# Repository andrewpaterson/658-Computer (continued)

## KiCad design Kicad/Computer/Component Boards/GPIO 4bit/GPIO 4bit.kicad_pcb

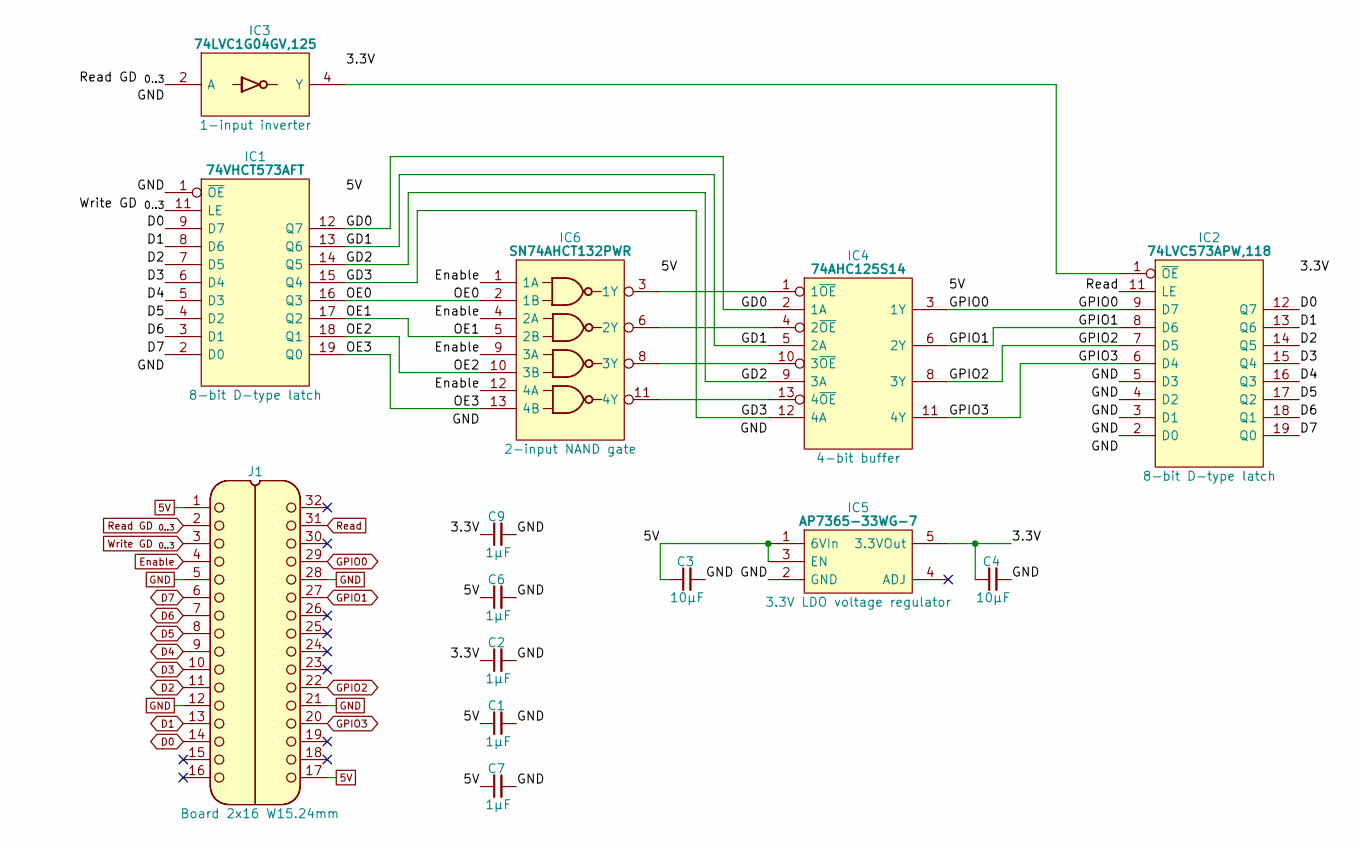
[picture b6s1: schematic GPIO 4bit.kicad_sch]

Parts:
C1, C2, C6, C7, C9: 1μF; C_0805
C3, C4: 10µF; C_0805
IC1: 74VHCT573AFT; SOP65P640X120-20N; Manufacturer_Part_Number 74VHCT573AFT; Mouser Part Number N/A
IC2: 74LVC573APW,118; SOP65P640X110-20N; Mouser Part Number 771-74LVC573APW-T
IC3: 74LVC1G04GV,125; SOT95P275X110-5N; Manufacturer_Part_Number 74LVC1G04GV,125; Mouser Part Number 771-74LVC1G04GV
IC4: 74AHC125S14; SOIC127P600X173-14N; Manufacturer_Part_Number 74AHC125S14-13; Mouser Part Number 621-74AHC125S14-13
IC5: AP7365-33WG-7; SOT95P285X130-5N; Manufacturer_Part_Number AP7365-33WG-7; Mouser Part Number 621-AP7365-33WG-7
IC6: SN74AHCT132PWR; SOP65P640X120-14N; Manufacturer_Part_Number SN74AHCT132PWR; Mouser Part Number 595-SN74AHCT132PWR
J1: Board 2x16 W15.24mm; DIP-32_Board_W15.24mm

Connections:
5V: C1.1, C3.1, C6.1, C7.1, IC1.20 (5V), IC4.14 (VCC), IC5.1 (6VIn), IC5.3 (EN), IC6.14 (5V), J1.1, J1.17
/3.3V: C2.1, C4.1, C9.1, IC2.20 (3V), IC3.5 (3V), IC5.5 (3.3VOut)
/GD0: IC1.12 (Q7), IC4.2 (1A)
/GD1: IC1.13 (Q6), IC4.5 (2A)
/GD2: IC1.14 (Q5), IC4.9 (3A)
/GD3: IC1.15 (Q4), IC4.12 (4A)
/OE0: IC1.16 (Q3), IC6.2 (1B)
/OE1: IC1.17 (Q2), IC6.5 (2B)
/OE2: IC1.18 (Q1), IC6.10 (3B)
/OE3: IC1.19 (Q0), IC6.13 (4B)
D0: IC1.9 (D7), IC2.12 (Q7), J1.14
D1: IC1.8 (D6), IC2.13 (Q6), J1.13
D2: IC1.7 (D5), IC2.14 (Q5), J1.11
D3: IC1.6 (D4), IC2.15 (Q4), J1.10
D4: IC1.5 (D3), IC2.16 (Q3), J1.9
D5: IC1.4 (D2), IC2.17 (Q2), J1.8
D6: IC1.3 (D1), IC2.18 (Q1), J1.7
D7: IC1.2 (D0), IC2.19 (Q0), J1.6
Enable: IC6.1 (1A), IC6.4 (2A), IC6.9 (3A), IC6.12 (4A), J1.4
GND: C1.2, C2.2, C3.2, C4.2, C6.2, C7.2, C9.2, IC1.1 (~OE), IC1.10 (GND), IC2.2 (D0), IC2.3 (D1), IC2.4 (D2), IC2.5 (D3), IC2.10 (GND), IC3.3 (GND), IC4.7 (GND), IC5.2 (GND), IC6.7 (GND), J1.5, J1.12, J1.21, J1.28
GPIO0: IC2.9 (D7), IC4.3 (1Y), J1.29
GPIO1: IC2.8 (D6), IC4.6 (2Y), J1.27
GPIO2: IC2.7 (D5), IC4.8 (3Y), J1.22
GPIO3: IC2.6 (D4), IC4.11 (4Y), J1.20
unnamed: IC2.1 (~OE), IC3.4 (Y)
unnamed: IC4.1 (1~OE), IC6.3 (1Y)
unnamed: IC4.4 (2~OE), IC6.6 (2Y)
unnamed: IC4.10 (3~OE), IC6.8 (3Y)
unnamed: IC4.13 (4~OE), IC6.11 (4Y)
Read: IC2.11 (LE), J1.31
Read GD _{0..3}: IC3.2 (A), J1.2
Write GD _{0..3}: IC1.11 (LE), J1.3

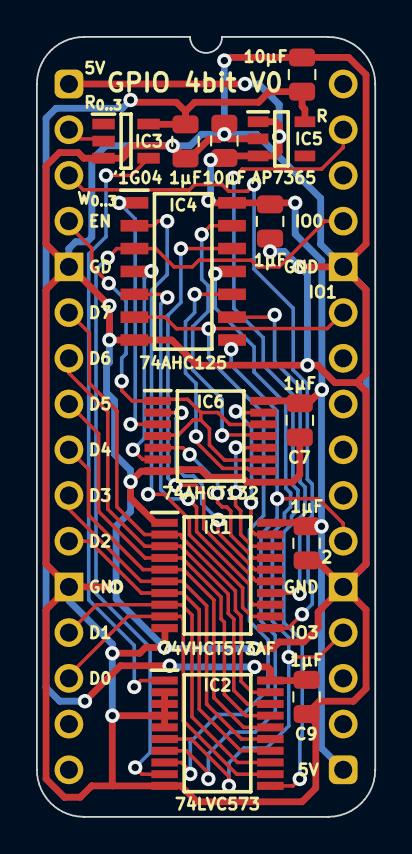
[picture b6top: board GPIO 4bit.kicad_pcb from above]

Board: 2 copper layers, 18.8 x 43.3 mm, 14 parts (0 on the bottom side), 32 nets.

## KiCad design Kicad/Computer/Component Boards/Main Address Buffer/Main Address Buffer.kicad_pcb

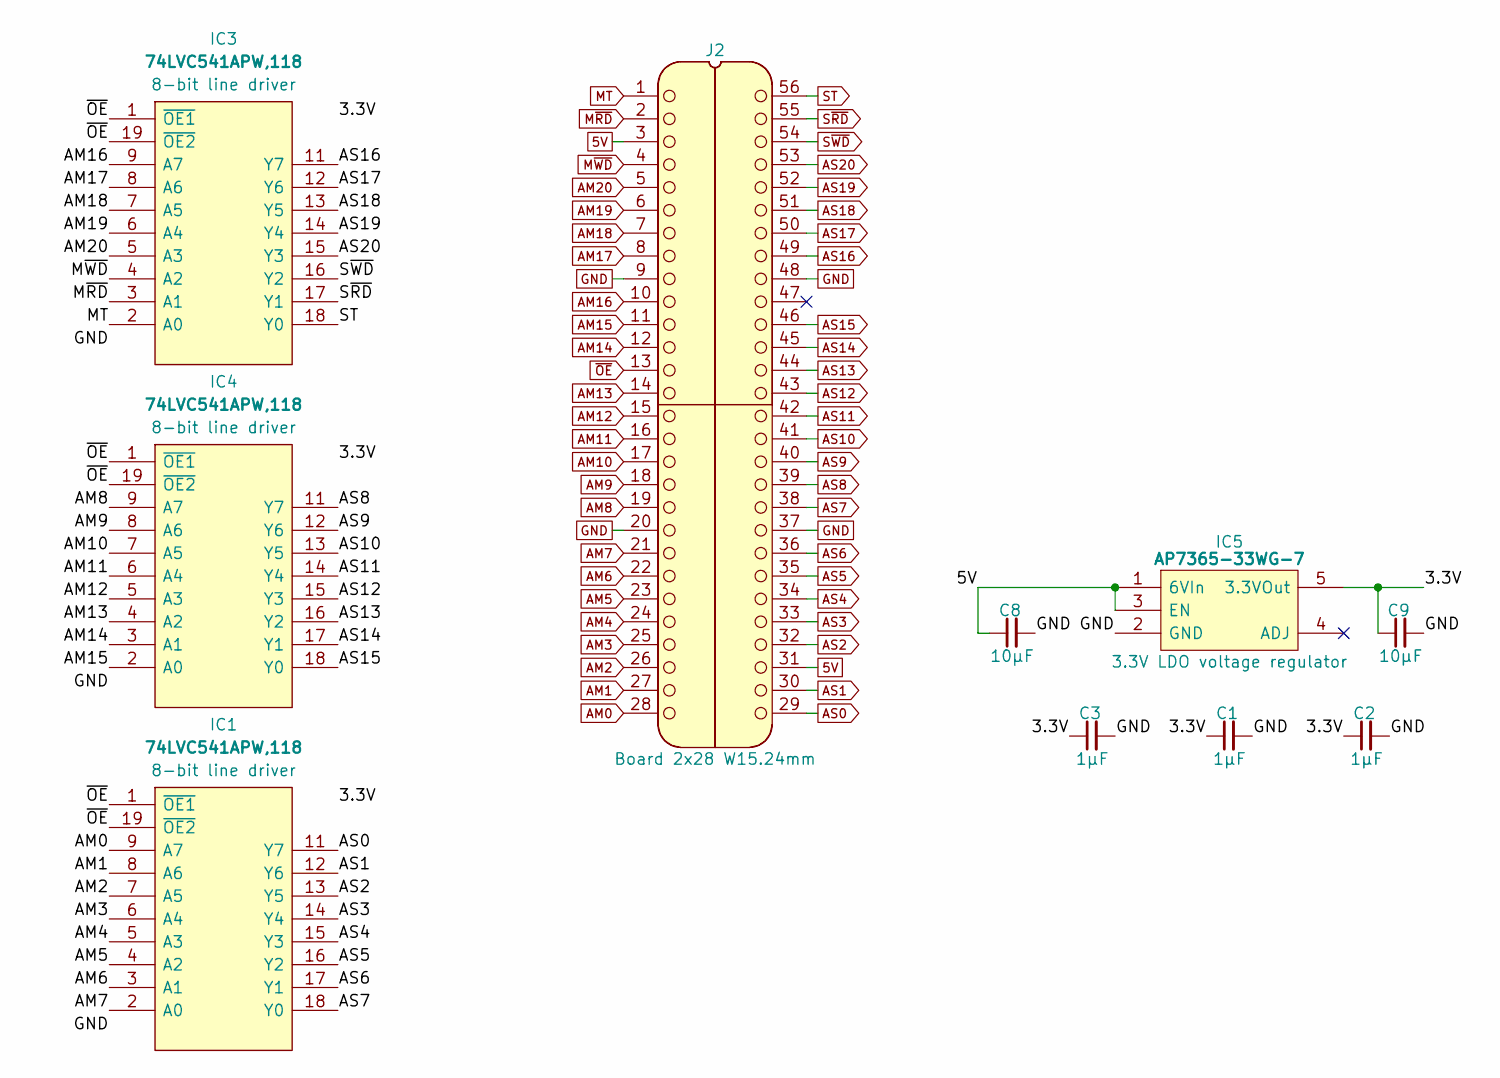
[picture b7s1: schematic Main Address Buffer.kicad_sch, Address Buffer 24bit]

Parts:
C1, C2, C3: 1μF; C_0805
C8, C9: 10µF; C_0805
IC1, IC3, IC4: 74LVC541APW,118; SOP65P640X110-20N; Mouser Part Number 771-74LVC541APW-T
IC5: AP7365-33WG-7; SOT95P285X130-5N; Manufacturer_Part_Number AP7365-33WG-7; Mouser Part Number 621-AP7365-33WG-7
J2: Board 2x28 W15.24mm; DIP-56_Board_W15.24mm

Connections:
5V: C8.1, IC5.1 (6VIn), IC5.3 (EN), J2.3, J2.31
/3.3V: C1.1, C2.1, C3.1, C9.1, IC1.20 (3V), IC3.20 (3V), IC4.20 (3V), IC5.5 (3.3VOut)
AM0: IC1.9 (A7), J2.28
AM1: IC1.8 (A6), J2.27
AM2: IC1.7 (A5), J2.26
AM3: IC1.6 (A4), J2.25
AM4: IC1.5 (A3), J2.24
AM5: IC1.4 (A2), J2.23
AM6: IC1.3 (A1), J2.22
AM7: IC1.2 (A0), J2.21
AM8: IC4.9 (A7), J2.19
AM9: IC4.8 (A6), J2.18
AM10: IC4.7 (A5), J2.17
AM11: IC4.6 (A4), J2.16
AM12: IC4.5 (A3), J2.15
AM13: IC4.4 (A2), J2.14
AM14: IC4.3 (A1), J2.12
AM15: IC4.2 (A0), J2.11
AM16: IC3.9 (A7), J2.10
AM17: IC3.8 (A6), J2.8
AM18: IC3.7 (A5), J2.7
AM19: IC3.6 (A4), J2.6
AM20: IC3.5 (A3), J2.5
AS0: IC1.11 (Y7), J2.29
AS1: IC1.12 (Y6), J2.30
AS2: IC1.13 (Y5), J2.32
AS3: IC1.14 (Y4), J2.33
AS4: IC1.15 (Y3), J2.34
AS5: IC1.16 (Y2), J2.35
AS6: IC1.17 (Y1), J2.36
AS7: IC1.18 (Y0), J2.38
AS8: IC4.11 (Y7), J2.39
AS9: IC4.12 (Y6), J2.40
AS10: IC4.13 (Y5), J2.41
AS11: IC4.14 (Y4), J2.42
AS12: IC4.15 (Y3), J2.43
AS13: IC4.16 (Y2), J2.44
AS14: IC4.17 (Y1), J2.45
AS15: IC4.18 (Y0), J2.46
AS16: IC3.11 (Y7), J2.49
AS17: IC3.12 (Y6), J2.50
AS18: IC3.13 (Y5), J2.51
AS19: IC3.14 (Y4), J2.52
AS20: IC3.15 (Y3), J2.53
GND: C1.2, C2.2, C3.2, C8.2, C9.2, IC1.10 (GND), IC3.10 (GND), IC4.10 (GND), IC5.2 (GND), J2.9, J2.20, J2.37, J2.48
MT: IC3.2 (A0), J2.1
M~RD: IC3.3 (A1), J2.2
M~WD: IC3.4 (A2), J2.4
ST: IC3.18 (Y0), J2.56
S~RD: IC3.17 (Y1), J2.55
S~WD: IC3.16 (Y2), J2.54
~OE: IC1.1 (~OE1), IC1.19 (~OE2), IC3.1 (~OE1), IC3.19 (~OE2), IC4.1 (~OE1), IC4.19 (~OE2), J2.13

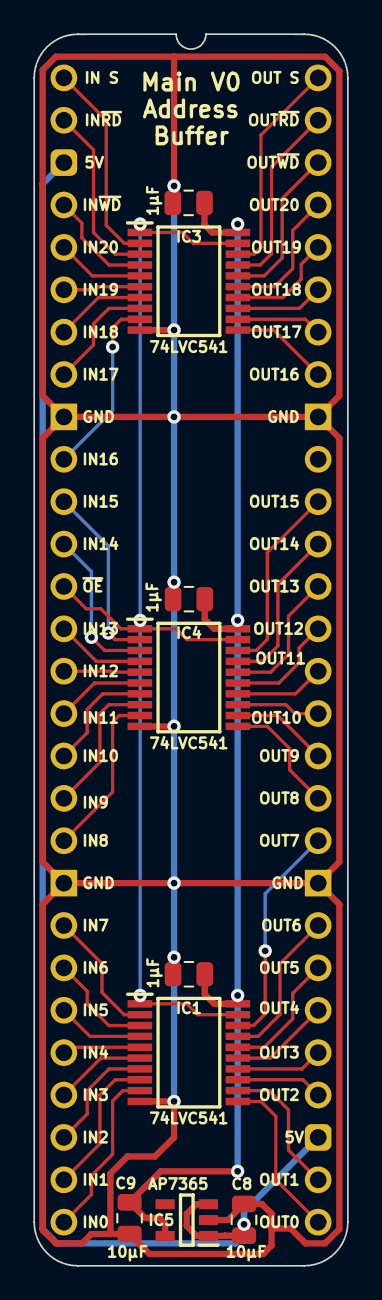
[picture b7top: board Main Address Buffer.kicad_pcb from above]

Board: 2 copper layers, 18.8 x 73.8 mm, 10 parts (0 on the bottom side), 52 nets.

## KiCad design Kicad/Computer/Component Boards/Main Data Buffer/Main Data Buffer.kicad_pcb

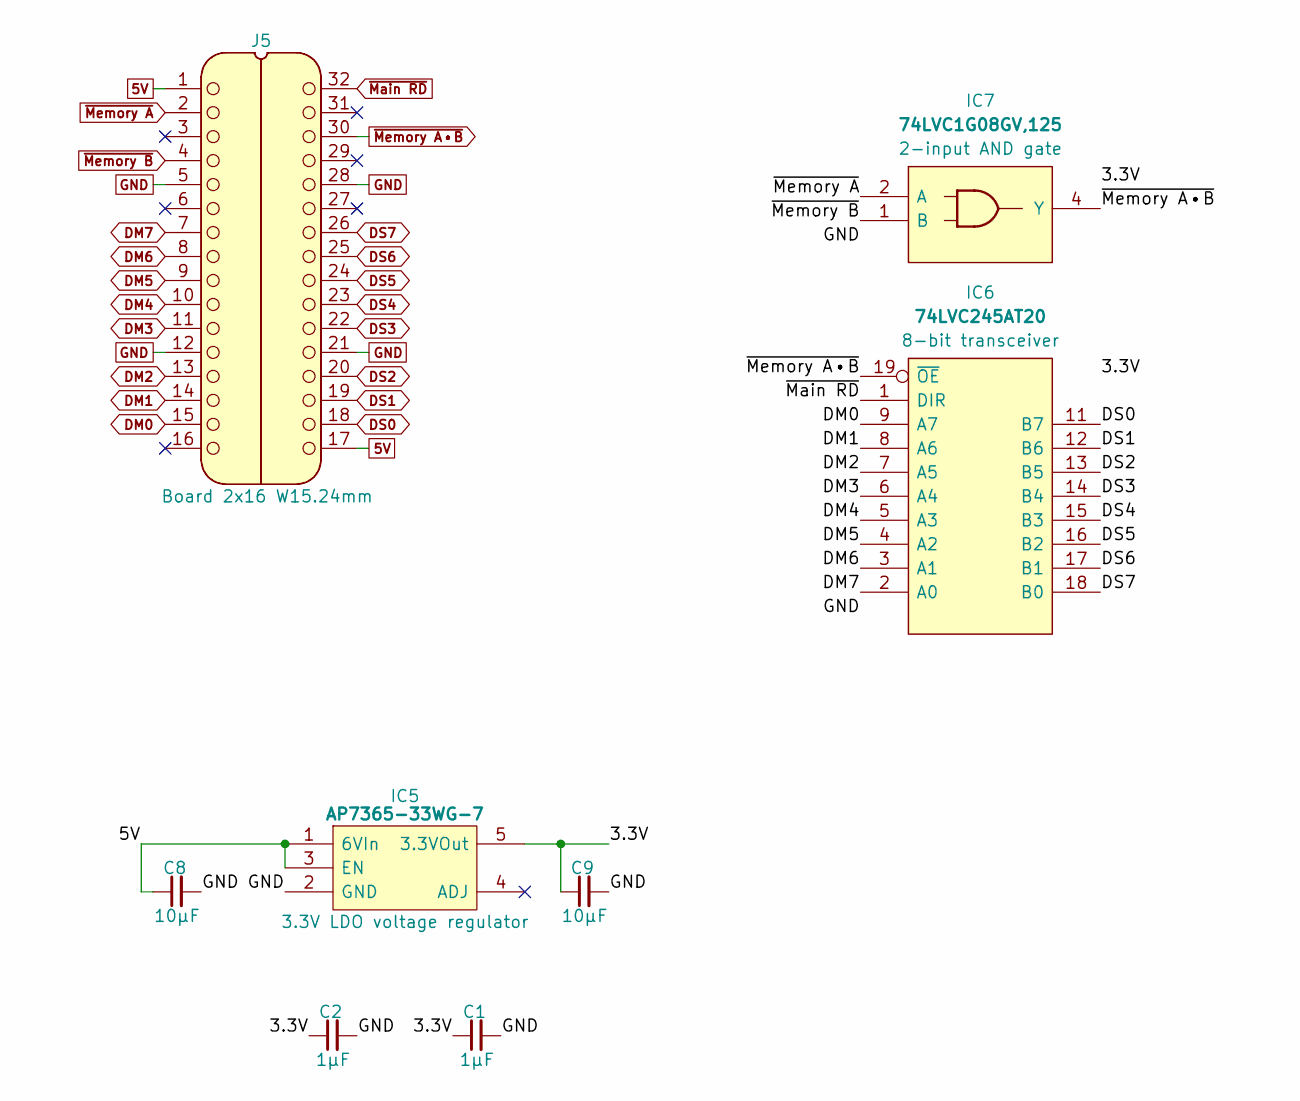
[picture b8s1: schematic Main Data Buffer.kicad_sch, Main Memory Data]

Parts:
C1, C2: 1μF; C_0805
C8, C9: 10µF; C_0805
IC5: AP7365-33WG-7; SOT95P285X130-5N; Manufacturer_Part_Number AP7365-33WG-7; Mouser Part Number 621-AP7365-33WG-7
IC6: 74LVC245AT20; SOP65P640X120-20N; Manufacturer_Part_Number 74LVC245AT20-13; Mouser Part Number 621-74LVC245AT20-13
IC7: 74LVC1G08GV,125; SOT95P275X110-5N; Manufacturer_Part_Number 74LVC1G08GV,125; Mouser Part Number 771-74LVC1G08GV
J5: Board 2x16 W15.24mm; DIP-32_Board_W15.24mm

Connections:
5V: C8.1, IC5.1 (6VIn), IC5.3 (EN), J5.1, J5.17
/3.3V: C1.1, C2.1, C9.1, IC5.5 (3.3VOut), IC6.20 (3V), IC7.5 (3V)
DM0: IC6.9 (A7), J5.15
DM1: IC6.8 (A6), J5.14
DM2: IC6.7 (A5), J5.13
DM3: IC6.6 (A4), J5.11
DM4: IC6.5 (A3), J5.10
DM5: IC6.4 (A2), J5.9
DM6: IC6.3 (A1), J5.8
DM7: IC6.2 (A0), J5.7
DS0: IC6.11 (B7), J5.18
DS1: IC6.12 (B6), J5.19
DS2: IC6.13 (B5), J5.20
DS3: IC6.14 (B4), J5.22
DS4: IC6.15 (B3), J5.23
DS5: IC6.16 (B2), J5.24
DS6: IC6.17 (B1), J5.25
DS7: IC6.18 (B0), J5.26
GND: C1.2, C2.2, C8.2, C9.2, IC5.2 (GND), IC6.10 (GND), IC7.3 (GND), J5.5, J5.12, J5.21, J5.28
~Main RD: IC6.1 (DIR), J5.32
~Memory A: IC7.2 (A), J5.2
~Memory A•B: IC6.19 (~OE), IC7.4 (Y), J5.30
~Memory B: IC7.1 (B), J5.4

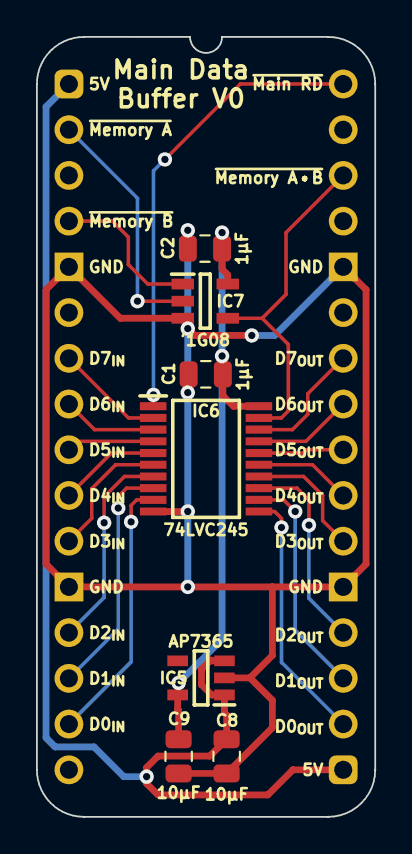
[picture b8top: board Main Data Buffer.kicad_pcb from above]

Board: 2 copper layers, 18.8 x 43.3 mm, 8 parts (0 on the bottom side), 23 nets.
